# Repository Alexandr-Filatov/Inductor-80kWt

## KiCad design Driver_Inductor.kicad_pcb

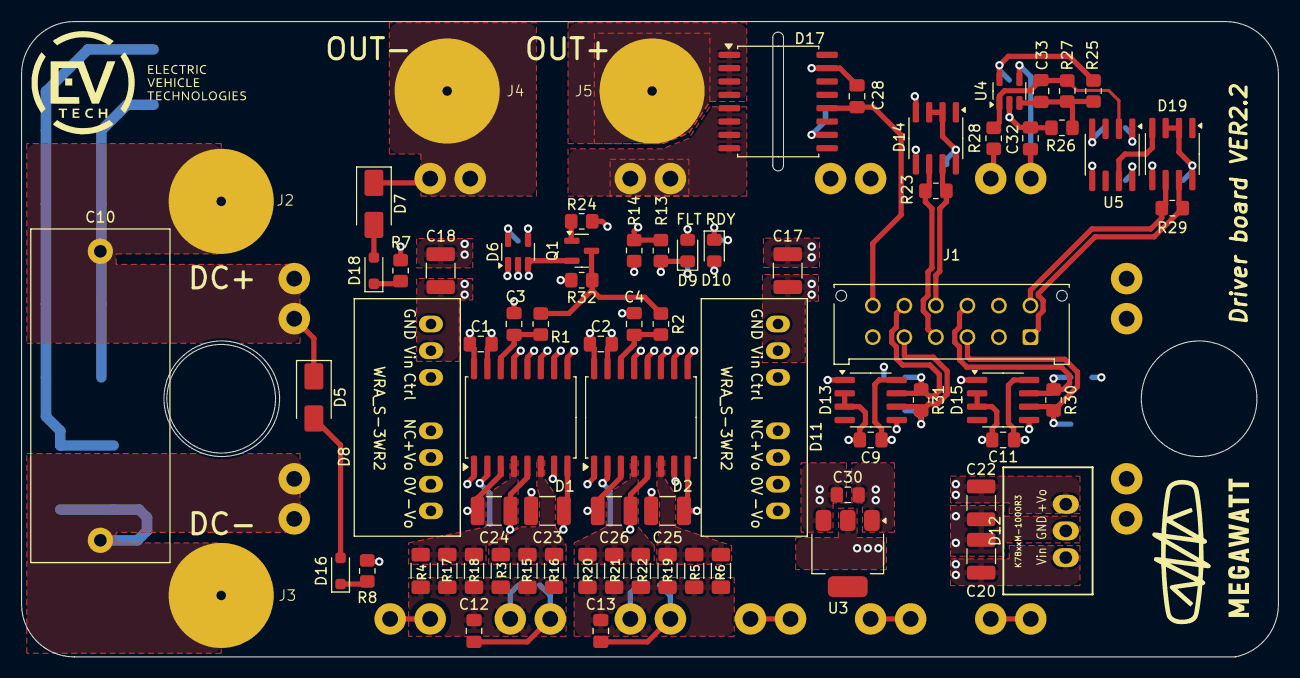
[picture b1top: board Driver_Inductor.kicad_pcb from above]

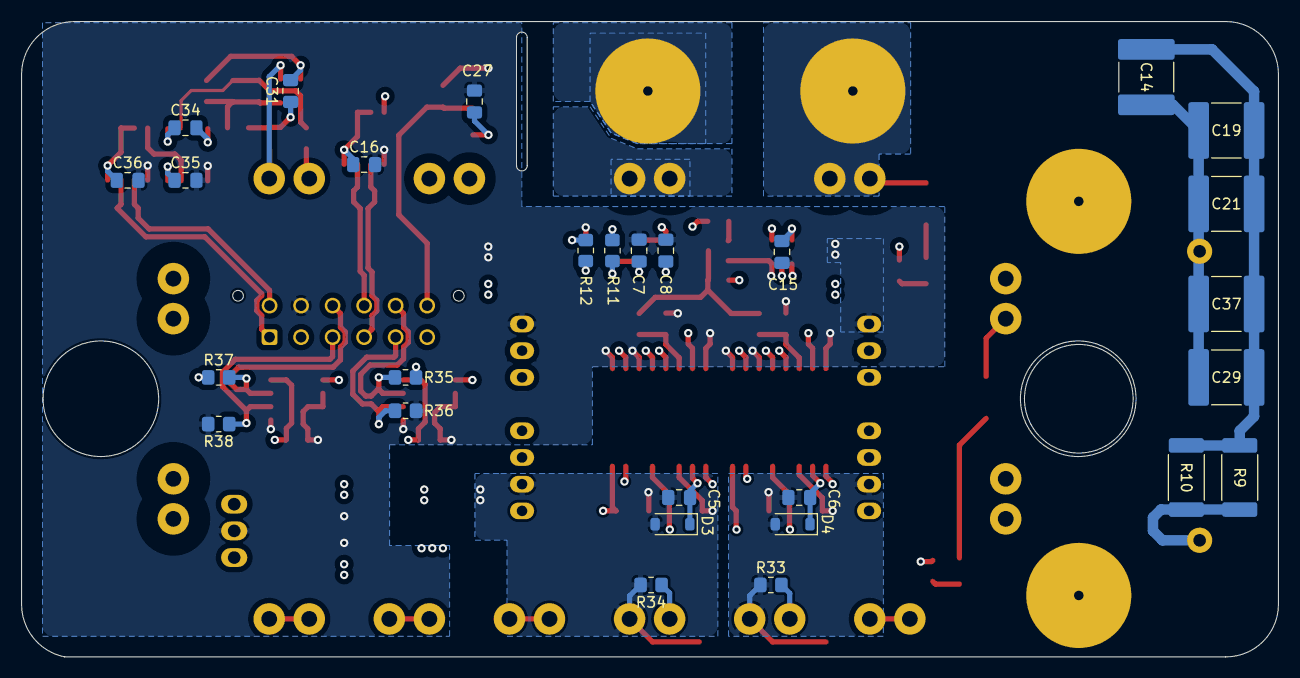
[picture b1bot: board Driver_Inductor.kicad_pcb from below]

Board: 6 copper layers, 119.6 x 60.5 mm, 104 parts (28 on the bottom side), 58 nets.

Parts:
C1, C2: 0.1u; C_0805_2012Metric_Pad1.18x1.45mm_HandSolder
C3, C4, C7, C8, C33: 56p; C_0805_2012Metric_Pad1.18x1.45mm_HandSolder
C5, C6: 100p; C_0805_2012Metric_Pad1.18x1.45mm_HandSolder
C9, C11, C15, C16, C30, C31, C34, C35, C36: 2.2u; C_0805_2012Metric_Pad1.18x1.45mm_HandSolder
C10: 1u; C_Rect_L31.5mm_W13.0mm_P27.50mm_MKS4
C12, C13: 47n; C_0805_2012Metric_Pad1.18x1.45mm_HandSolder
C14, C19, C21, C29, C37: 1u; C_2220_5750Metric_Pad1.97x5.40mm_HandSolder
C17, C18, C20, C22, C23, C24, C25, C26: 10u; C_1210_3225Metric_Pad1.33x2.70mm_HandSolder
C27: 4.7u; C_0805_2012Metric_Pad1.18x1.45mm_HandSolder
C28: 1n; C_0805_2012Metric_Pad1.18x1.45mm_HandSolder
C32: 10n; C_0805_2012Metric_Pad1.18x1.45mm_HandSolder
D1, D2: NSI6651ASC-DSWR; SOIC-16W_7.5x10.3mm_P1.27mm
D3, D4: MMSZ5240B; D_SOD-123
D5, D7: MURS160; D_SMA
D6: SN74AHC1G08DBVR; SOT-23-5
D8, D11: WRA1215S-3WR2; WRA_S-3WR2
D9: FLT; LED_0805_2012Metric_Pad1.15x1.40mm_HandSolder
D10: RDY; LED_0805_2012Metric_Pad1.15x1.40mm_HandSolder
D12: K7805M-1000R3; K78xxM-1000R3
D13, D14, D15: SN65HVD3082EDR; SOIC-8_3.9x4.9mm_P1.27mm
D16, D18: 1SMB5919B; D_SOD-323_HandSoldering
D17: NSM2011-50B5R-DSWR; SOIC-16W_7.5x10.3mm_P1.27mm
D19: ADM3485E; SOIC-8_3.9x4.9mm_P1.27mm
D20: GD50FFY120C5S
J1: Control_A; Molex_Micro-Fit_3.0_43045-1212_2x06_P3.00mm_Vertical
J2: DC+; Bush_M4
J3: DC-; Bush_M4
J4: OUT1; Bush_M4
J5: OUT2; Bush_M4
Q1: BC817; SOT-23
R1, R2, R23, R29, R30, R31: 120; R_0805_2012Metric_Pad1.20x1.40mm_HandSolder
R3, R4, R5, R6, R15, R16, R17, R18, R19, R20, R21, R22: 47; R_1206_3216Metric_Pad1.30x1.75mm_HandSolder
R7, R8: 1.6k; R_0805_2012Metric_Pad1.20x1.40mm_HandSolder
R9, R10: 0.5; R_2512_6332Metric_Pad1.40x3.35mm_HandSolder
R11, R14, R32: 1k; R_0805_2012Metric_Pad1.20x1.40mm_HandSolder
R12, R35, R36, R37, R38: 560; R_0805_2012Metric_Pad1.20x1.40mm_HandSolder
R13, R25, R26, R27, R33, R34: 10k; R_0805_2012Metric_Pad1.20x1.40mm_HandSolder
R24: 4.7k; R_0805_2012Metric_Pad1.20x1.40mm_HandSolder
R28: 2.2k; R_0805_2012Metric_Pad1.20x1.40mm_HandSolder
U3: LM1117GS-5.0; SOT-223
U4: LMV7219M5; SOT-23-5
U5: SCM3728ASA; SOIC-8_3.9x4.9mm_P1.27mm

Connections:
+5V: C1.2, C2.2, C9.1, C11.1, C15.1, C16.1, C22.1, C27.1, C35.1, C36.1, D1.15 (Vcc1), D2.15 (Vcc1), D6.5 (Vcc), D12.3 (+Vo), D13.8 (VCC), D14.2 (RE), D14.3 (DE), D14.8 (VCC), D15.8 (VCC), D17.10 (VCC), D19.2 (RE), D19.3 (DE), D19.8 (VCC), R11.2, R13.2, R14.2, R32.2, R35.1, R37.1, U5.8 (VDD2)
+5VP: C31.1, C34.1, R25.2, U3.2 (VO), U4.5 (V+), U5.1 (VDD1)
+15V: C17.1, C18.1, C20.1, D8.2 (Vin), D11.2 (Vin), D12.1 (Vin), J1.2
+15V_H: C26.2, D2.5 (Vcc2), D11.6 (+VO)
+15V_L: C24.2, D1.5 (Vcc2), D8.6 (+VO)
-15V_H: C25.1, C30.2, C31.2, C32.2, C34.2, D2.1 (Vee2), D2.8 (Vee2), D11.8 (-Vo), R26.1, U3.1 (GND), U4.2 (V-), U5.4 (GND1)
-15V_L: C23.1, D1.1 (Vee2), D1.8 (Vee2), D8.8 (-Vo)
-VDC: C10.2, D20.27 (DC-), D20.28 (DC-), J3.1, R9.2, R10.2
Current: C28.1, D17.12 (VOUT), J1.12
DESAT_H: C10.1, C14.1, C19.1, C21.1, C29.1, C37.1, D5.1 (K), D20.25 (DC+), D20.26 (DC+), J2.1
E2: C6.2, C12.2, C23.2, C24.1, D1.3 (GND2), D4.2 (A), D8.7 (0V), D20.4 (E2), R33.1
E3: C5.2, C13.1, C25.2, C26.1, C30.1, D2.3 (GND2), D3.2 (A), D11.7 (0V), D20.6 (E3), R34.2, U3.3 (VI)
FLT: C7.1, D1.13 (~FLT), D2.13 (~FLT), D6.2 (A), D9.1 (K), R13.1
Fault_N: D14.7 (B), J1.10, R23.1
Fault_P: D14.6 (A), J1.4, R23.2
G2: C12.1, D1.7 (CLAMP), D20.3 (G2), R3.1, R4.1, R15.1, R16.1, R17.1, R18.1, R33.2
G3: C13.2, D2.7 (CLAMP), D20.5 (G3), R5.1, R6.1, R19.1, R20.1, R21.1, R22.1, R34.1
GND: C1.1, C2.1, C3.1, C4.1, C7.2, C8.2, C9.2, C11.2, C15.2, C16.2, C17.2, C18.2, C20.2, C22.2, C27.2, C28.2, C35.2, C36.2, D1.9 (GND1), D1.11 (IN-), D1.16 (TEST), D2.9 (GND1), D2.11 (IN-), D2.16 (TEST), D6.3 (GND), D8.1 (GND), D10.1 (K), D11.1 (GND), D12.2 (GND), D13.2 (~RE), D13.3 (DE), D13.5 (GND), D14.5 (GND), D15.2 (~RE), D15.3 (DE), D15.5 (GND), D17.15 (GND), D19.5 (GND), J1.8, Q1.2 (S), R36.2, R38.2, U5.5 (GND2)
NTC1: C32.1, D20.17 (NTC1), U4.4 (-)
NTC2: D20.18 (NTC2), R28.2
unnamed: C14.2, C19.2, C21.2, C29.2, C37.2, R9.1, R10.1
unnamed: C6.1, D1.2 (DESAT), D4.1 (K), R7.2
unnamed: D1.10 (IN+), D13.1 (RO)
unnamed: D1.4 (OUTH), R4.2, R17.2, R18.2
unnamed: D1.6 (OUTL), R3.2, R15.2, R16.2
unnamed: C3.2, D1.14 (~RST), R1.2
unnamed: C5.1, D2.2 (DESAT), D3.1 (K), R8.2
unnamed: D2.4 (OUTH), R20.2, R21.2, R22.2
unnamed: D2.6 (OUTL), R5.2, R6.2, R19.2
unnamed: C4.2, D2.14 (~RST), R2.2
unnamed: D9.2 (A), R11.1
unnamed: D10.2 (A), R12.1
unnamed: D6.4 (Y), D14.4 (DI)
unnamed: D2.10 (IN+), D15.1 (RO)
unnamed: D5.2 (A), D16.2 (A)
unnamed: D16.1 (K), R8.1
unnamed: D7.2 (A), D18.2 (A)
unnamed: D18.1 (K), R7.1
unnamed: D19.4 (DI), U5.7 (VOA)
unnamed: D20.1 (G1), D20.2 (E1)
unnamed: D20.7 (G4), D20.8 (E4)
unnamed: D20.9 (G5), D20.10 (E5)
unnamed: D20.11 (G6), D20.12 (E6)
unnamed: Q1.1 (G), R24.2
unnamed: C33.1, R25.1, R26.2, R27.1, U4.3 (+)
unnamed: C33.2, R27.2, R28.1, U4.1, U5.2 (VIA)
OUT1: D7.1 (K), D20.23 (OUT1), D20.24 (OUT1), J4.1
OUT2: D17.5 (IP-), D17.6 (IP-), D17.7 (IP-), D17.8 (IP-), D20.21 (OUT2), D20.22 (OUT2)
OUT2_Sens: D17.1 (IP+), D17.2 (IP+), D17.3 (IP+), D17.4 (IP+), J5.1
PWM1_N: D15.7 (B), J1.9, R30.1, R37.2
PWM1_P: D15.6 (A), J1.3, R30.2, R38.1
PWM2_N: D13.7 (B), J1.11, R31.1, R35.2
PWM2_P: D13.6 (A), J1.5, R31.2, R36.1
RDY: C8.1, D1.12 (RDY), D2.12 (RDY), D6.1 (B), R12.2, R14.1
RST: Q1.3 (D), R1.1, R2.1, R32.1
Reset: J1.6, R24.1
Temp_N: D19.7 (B), J1.1, R29.1
Temp_P: D19.6 (A), J1.7, R29.2

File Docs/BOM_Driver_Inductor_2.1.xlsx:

Reference | Value | Footprint | Qty | Description
C1,C2 | 0.1u | Capacitor_SMD:C_0805_2012Metric_Pad1.18x1.45mm_HandSolder | 2 | Capacitor SMD
C3,C4,C7,C8,C33 | 56p | Capacitor_SMD:C_0805_2012Metric_Pad1.18x1.45mm_HandSolder | 5 | Capacitor SMD
C5,C6 | 100p | Capacitor_SMD:C_0805_2012Metric_Pad1.18x1.45mm_HandSolder | 2 | Capacitor SMD
C9,C11,C15,C16,C30,C31,C34,C35,C36 | 2.2u | Capacitor_SMD:C_0805_2012Metric_Pad1.18x1.45mm_HandSolder | 9 | Capacitor SMD
C10 | 1u | Capacitor_THT:C_Rect_L31.5mm_W13.0mm_P27.50mm_MKS4 | 1 | B32674D6105K000
C12,C13 | 47n | Capacitor_SMD:C_0805_2012Metric_Pad1.18x1.45mm_HandSolder | 2 | Capacitor SMD
C17,C18,C20,C22,C23,C24,C25,C26 | 10u | Capacitor_SMD:C_1210_3225Metric_Pad1.33x2.70mm_HandSolder | 8 | Capacitor SMD
C27 | 4.7u | Capacitor_SMD:C_0805_2012Metric_Pad1.18x1.45mm_HandSolder | 1 | Capacitor SMD
C28 | 1n | Capacitor_SMD:C_0805_2012Metric_Pad1.18x1.45mm_HandSolder | 1 | Capacitor SMD
C32 | 10n | Capacitor_SMD:C_0805_2012Metric_Pad1.18x1.45mm_HandSolder | 1 | Capacitor SMD
D1,D2 | NSI6651ASC-DSWR | Package_SO:SOIC-16W_7.5x10.3mm_P1.27mm | 2 | Gate driver
D3,D4 | MMSZ5240B | Diode_SMD:D_SOD-123 | 2 | Zener Diode
D5,D7 | MURS160 | Diode_SMD:D_SMA | 2 | Fast diode
D6 | SN74AHC1G08DBVR | Package_TO_SOT_SMD:SOT-23-5 | 1
D8,D11 | WRA1215S-3WR2 | Mornsun:WRA_S-3WR2 | 2 | DCDC
D9 | EC04-0805QRC/E-AV | LED_SMD:LED_0805_2012Metric_Pad1.15x1.40mm_HandSolder | 1 | LED
D10 | LTST-C171TBKT | LED_SMD:LED_0805_2012Metric_Pad1.15x1.40mm_HandSolder | 1 | LED
D12 | K7805M-1000R3 | Mornsun:K78xxM-1000R3 | 1 | DCDC
D13,D14,D15,D19 | SN65HVD3082EDR | Package_SO:SOIC-8_3.9x4.9mm_P1.27mm | 4 | RS485
D16,D18 | 1SMB5919B | Diode_SMD:D_SOD-323_HandSoldering | 2 | Zener Diode
D17 | NSM2011-50B5R-DSWR | Package_SO:SOIC-16W_7.5x10.3mm_P1.27mm | 1 | Current Sensor
J1 | SCT3001WV-2x06P | Connector_Molex:Molex_Micro-Fit_3.0_43045-1212_2x06_P3.00mm_Vertical | 1 | Connector
J2 | DC+ | Connector_My:Bush_M4 | 1 | Connector
J3 | DC- | Connector_My:Bush_M4 | 1 | Connector
J4 | OUT1 | Connector_My:Bush_M4 | 1 | Connector
J5 | OUT2 | Connector_My:Bush_M4 | 1 | Connector
Q1 | BC817 | Package_TO_SOT_SMD:SOT-23 | 1 | Transistor
R1,R2,R23,R29,R30,R31 | 120 | Resistor_SMD:R_0805_2012Metric_Pad1.20x1.40mm_HandSolder | 6 | Resistor SMD
R3,R4,R5,R6,R15,R16,R17,R18,R19,R20,R21,R22 | 47 | Resistor_SMD:R_1206_3216Metric_Pad1.30x1.75mm_HandSolder | 12 | Resistor SMD
R7,R8 | 1.6k | Resistor_SMD:R_0805_2012Metric_Pad1.20x1.40mm_HandSolder | 2 | Resistor SMD
R11,R14,R32 | 1k | Resistor_SMD:R_0805_2012Metric_Pad1.20x1.40mm_HandSolder | 3 | Resistor SMD
R12,R35,R36,R37,R38 | 560 | Resistor_SMD:R_0805_2012Metric_Pad1.20x1.40mm_HandSolder | 5 | Resistor SMD
R13,R25,R26,R27,R33,R34 | 10k | Resistor_SMD:R_0805_2012Metric_Pad1.20x1.40mm_HandSolder | 6 | Resistor SMD
R24 | 4.7k | Resistor_SMD:R_0805_2012Metric_Pad1.20x1.40mm_HandSolder | 1 | Resistor SMD
R28 | 2.2k | Resistor_SMD:R_0805_2012Metric_Pad1.20x1.40mm_HandSolder | 1 | Resistor SMD
U3 | LM1117GS-5.0 | Package_TO_SOT_SMD:SOT-223 | 1 | DCDC
U4 | LMV7219M5 | Package_TO_SOT_SMD:SOT-23-5 | 1 | Comparator
U5 | SCM3728ASA | Package_SO:SOIC-8_3.9x4.9mm_P1.27mm | 1 | Digital isolator

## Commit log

2023-04-18 VER1.0
2023-10-03 Тестовая версия
2024-07-29 Заменил компаратор на пушпульный
2024-07-29 Сохранил изменения
2024-07-29 Сохранил изменения в схеме
2024-10-07 Убрал питание 3.3В
2024-10-08 Развел все дорожки
2024-10-09 Заменил в схеме символы питания
2024-10-31 VER2.0 Отправил в резонит
2024-10-31 VER2.0 Изменения: заменил 3D модель
2024-11-18 Изменения: добавил 5 вольтовые RS485 на вход драйверов
2024-11-19 Изменения: изменил BOM, сделал заказ
2025-02-22 VER2.1: внес все исправления для заказа в Китае
2025-02-25 VER2.1: исправил BOM, наименования в схеме и добавил папку с документами
2025-03-19 VER2.2: добавил цепь подавления колебаний
2025-03-20 VER2_Test: отправил в резонит
2025-03-24 VER2_Test: добавил новый BOM и в схеме заменил названия компонентов
2025-04-14 VER2.1: добавил файлы для сборки платы
2025-04-14 VER2.1: переименовал файлы для сборки
2025-05-15 VER2_Test: добавил монтажную схему
2025-05-21 VER2.1: добавил в доки схему
2025-07-09 VER2_Test: сделал схему в один лист красиво
2025-07-10 VER2_Test: добавил СБ и 3D модели
2025-07-10 VER2_Test: исправил децимальник в углу
2025-07-14 VER2_Test: исправил Э3
2025-07-16 VER2_Test: сделал спецификацию и оформил BOM
2025-07-16 VER2_Test: исправил спеку
2025-08-01 VER2_Test: добавил папку Drawings
2025-08-01 VER2_Test: добавил чертежи модуля
2025-08-21 VER2_Test: заменил источники на QA1
2025-08-22 VER2.3: оптимизировал трассировку + сделал BOM
2025-08-25 VER2.2: zero commit
2025-08-25 VER2.2: создал папку для производственных доков
2025-08-25 VER2.2: добавил гербера из резонита для китая
